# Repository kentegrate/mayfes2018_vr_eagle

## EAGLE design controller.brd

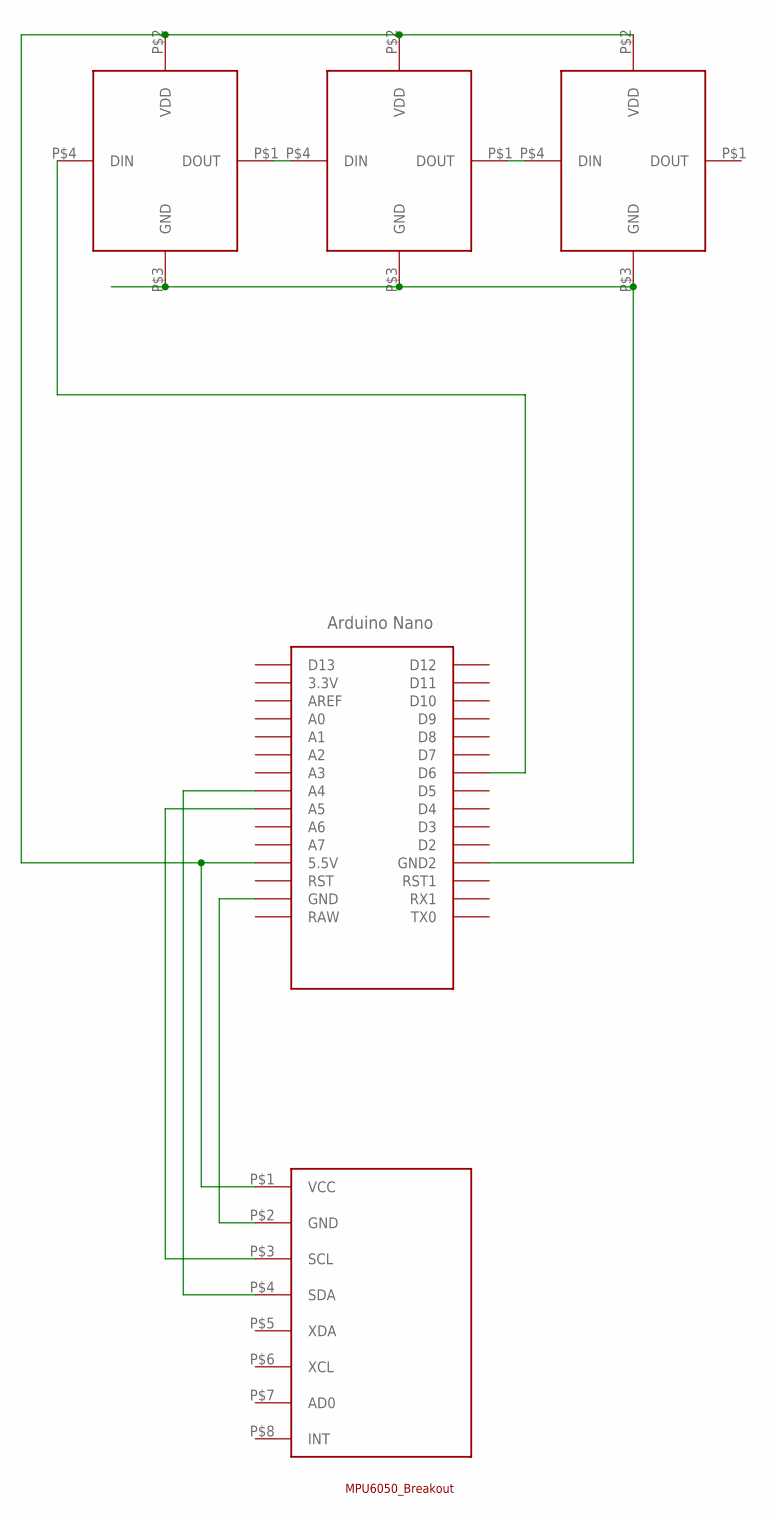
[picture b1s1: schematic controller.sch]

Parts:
U$1: NANO
U$2, U$3, U$4: NEOPIXEL_8MM
U$5: MPU6050_BREAKOUT; MPU6050

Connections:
unnamed: U$1.5V (5.5V), U$2.P$2 (VDD), U$3.P$2 (VDD), U$4.P$2 (VDD), U$5.P$1 (VCC)
unnamed: U$1.GND, U$5.P$2 (GND)
unnamed: U$1.A4, U$5.P$4 (SDA)
unnamed: U$1.A5, U$5.P$3 (SCL)
unnamed: U$1.D6, U$2.P$4 (DIN)
unnamed: U$1.GND1 (GND2), U$2.P$3 (GND), U$3.P$3 (GND), U$4.P$3 (GND)
unnamed: U$2.P$1 (DOUT), U$3.P$4 (DIN)
unnamed: U$3.P$1 (DOUT), U$4.P$4 (DIN)

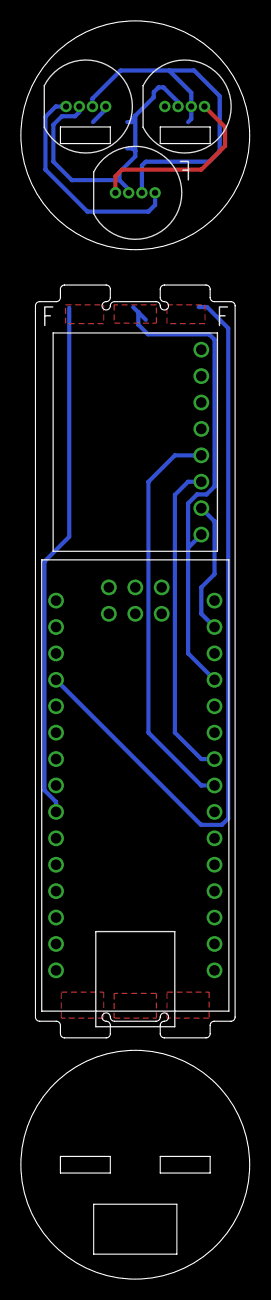
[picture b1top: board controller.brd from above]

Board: 2 copper layers, 22.0 x 121.0 mm, 5 parts (0 on the bottom side), 8 nets.

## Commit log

2018-04-10 fixed design based on prototype 0
